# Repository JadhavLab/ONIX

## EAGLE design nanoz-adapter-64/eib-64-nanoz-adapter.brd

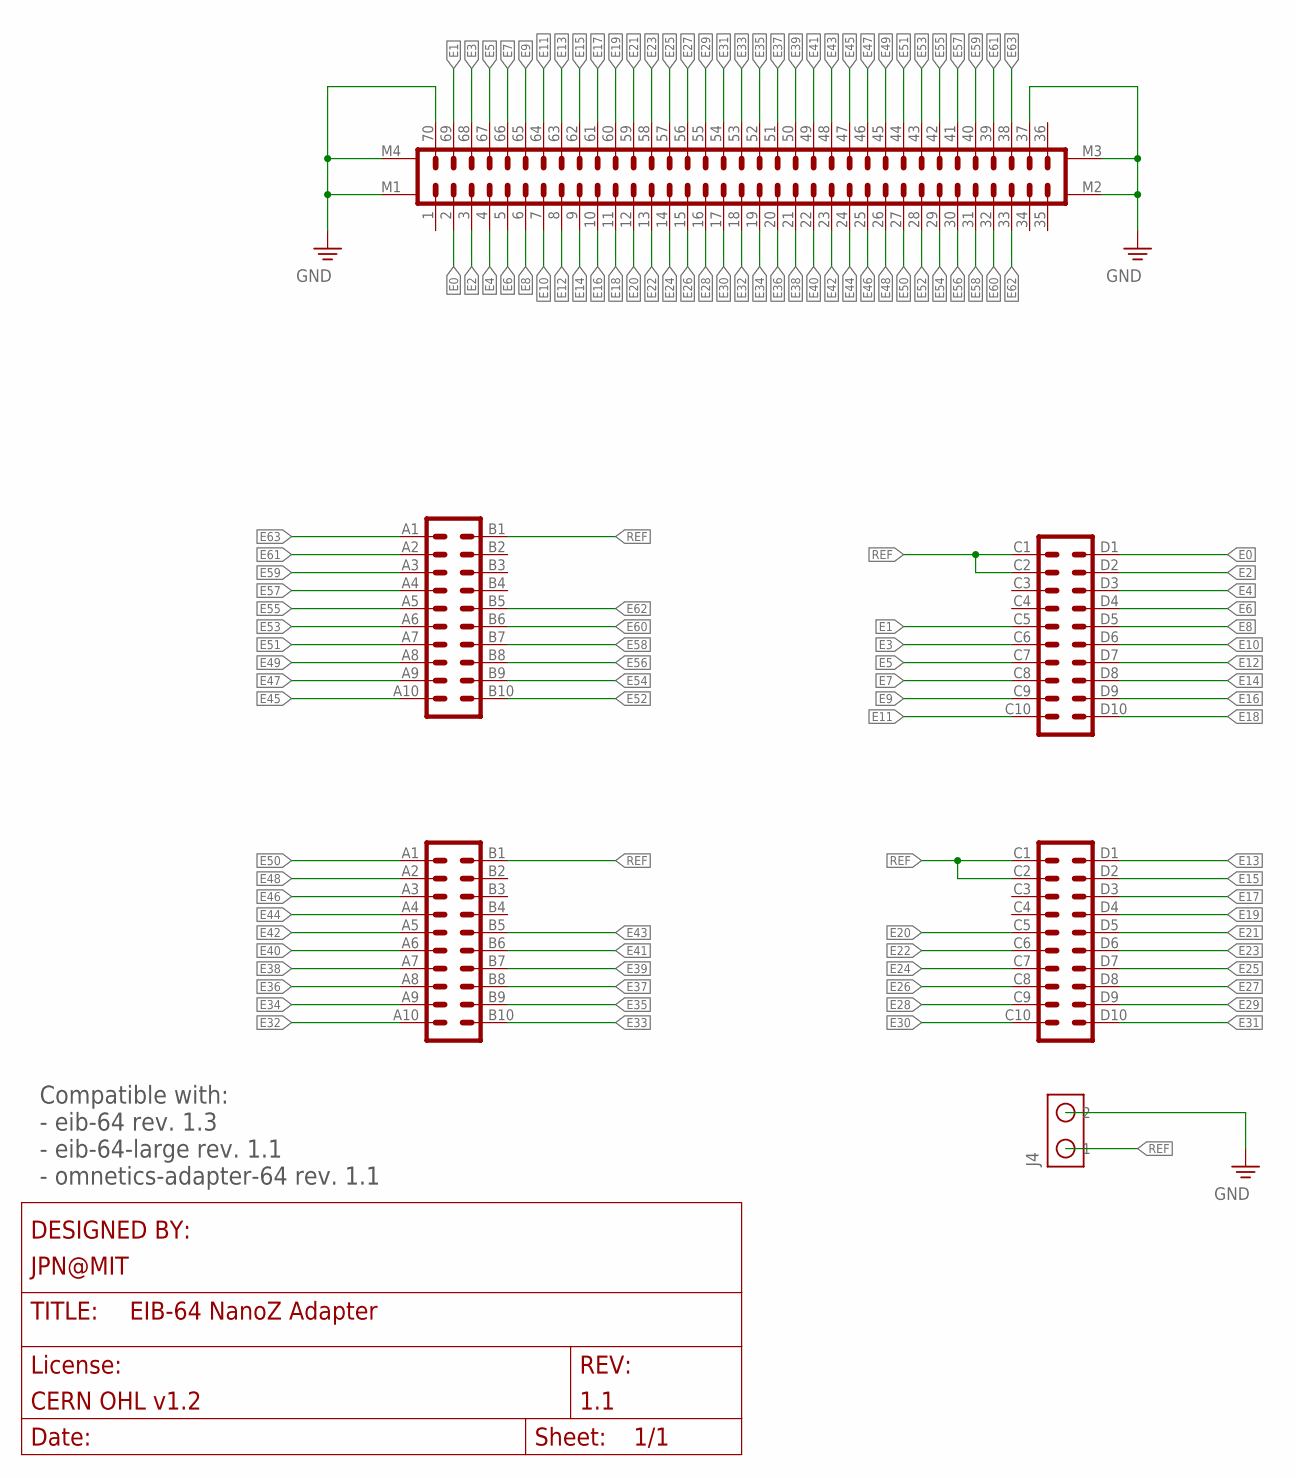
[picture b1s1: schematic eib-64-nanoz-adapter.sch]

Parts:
J1: DF40-REC; DF40-70HEAD
J2, J3: PINHD-4X10_MOLC-THRU; MOLC-110-11-S-Q
J4: SCREW2

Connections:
E0: J1.2, J2.D1 (20)
E1: J1.69, J2.C5 (5)
E2: J1.3, J2.D2 (19)
E3: J1.68, J2.C6 (6)
E4: J1.4, J2.D3 (18)
E5: J1.67, J2.C7 (7)
E6: J1.5, J2.D4 (17)
E7: J1.66, J2.C8 (8)
E8: J1.6, J2.D5 (16)
E9: J1.65, J2.C9 (9)
E10: J1.7, J2.D6 (15)
E11: J1.64, J2.C10 (10)
E12: J1.8, J2.D7 (14)
E13: J1.63, J3.D1 (20)
E14: J1.9, J2.D8 (13)
E15: J1.62, J3.D2 (19)
E16: J1.10, J2.D9 (12)
E17: J1.61, J3.D3 (18)
E18: J1.11, J2.D10 (11)
E19: J1.60, J3.D4 (17)
E20: J1.12, J3.C5 (5)
E21: J1.59, J3.D5 (16)
E22: J1.13, J3.C6 (6)
E23: J1.58, J3.D6 (15)
E24: J1.14, J3.C7 (7)
E25: J1.57, J3.D7 (14)
E26: J1.15, J3.C8 (8)
E27: J1.56, J3.D8 (13)
E28: J1.16, J3.C9 (9)
E29: J1.55, J3.D9 (12)
E30: J1.17, J3.C10 (10)
E31: J1.54, J3.D10 (11)
E32: J1.18, J3.A10 (10)
E33: J1.53, J3.B10 (11)
E34: J1.19, J3.A9 (9)
E35: J1.52, J3.B9 (12)
E36: J1.20, J3.A8 (8)
E37: J1.51, J3.B8 (13)
E38: J1.21, J3.A7 (7)
E39: J1.50, J3.B7 (14)
E40: J1.22, J3.A6 (6)
E41: J1.49, J3.B6 (15)
E42: J1.23, J3.A5 (5)
E43: J1.48, J3.B5 (16)
E44: J1.24, J3.A4 (4)
E45: J1.47, J2.A10 (10)
E46: J1.25, J3.A3 (3)
E47: J1.46, J2.A9 (9)
E48: J1.26, J3.A2 (2)
E49: J1.45, J2.A8 (8)
E50: J1.27, J3.A1 (1)
E51: J1.44, J2.A7 (7)
E52: J1.28, J2.B10 (11)
E53: J1.43, J2.A6 (6)
E54: J1.29, J2.B9 (12)
E55: J1.42, J2.A5 (5)
E56: J1.30, J2.B8 (13)
E57: J1.41, J2.A4 (4)
E58: J1.31, J2.B7 (14)
E59: J1.40, J2.A3 (3)
E60: J1.32, J2.B6 (15)
E61: J1.39, J2.A2 (2)
E62: J1.33, J2.B5 (16)
E63: J1.38, J2.A1 (1)
GND: J1.37, J1.70, J1.M1, J1.M2, J1.M3, J1.M4, J4.P$2 (2)
REF: J2.B1 (20), J2.C1 (1), J2.C2 (2), J3.B1 (20), J3.C1 (1), J3.C2 (2), J4.P$1 (1)

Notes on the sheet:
Compatible with: - eib-64 rev. 1.3 - eib-64-large rev. 1.1 - omnetics-adapter-64 rev. 1.1

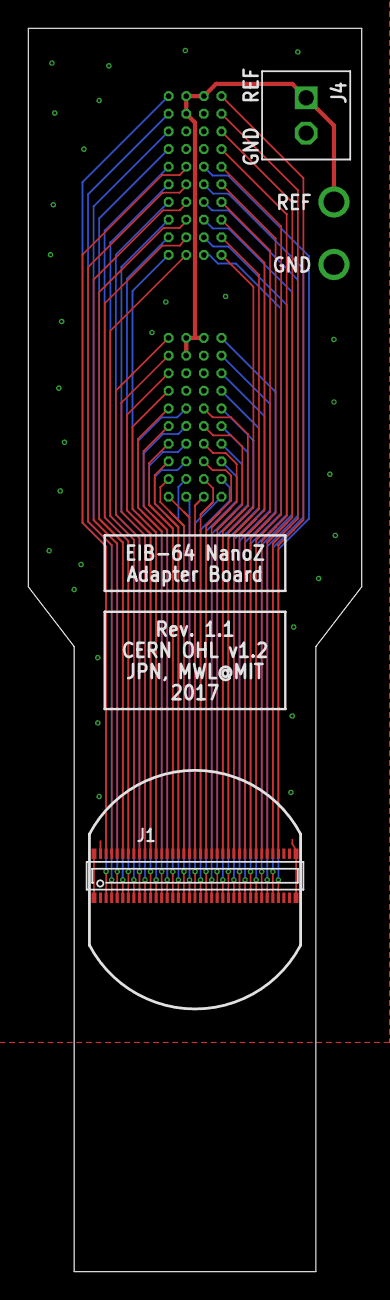
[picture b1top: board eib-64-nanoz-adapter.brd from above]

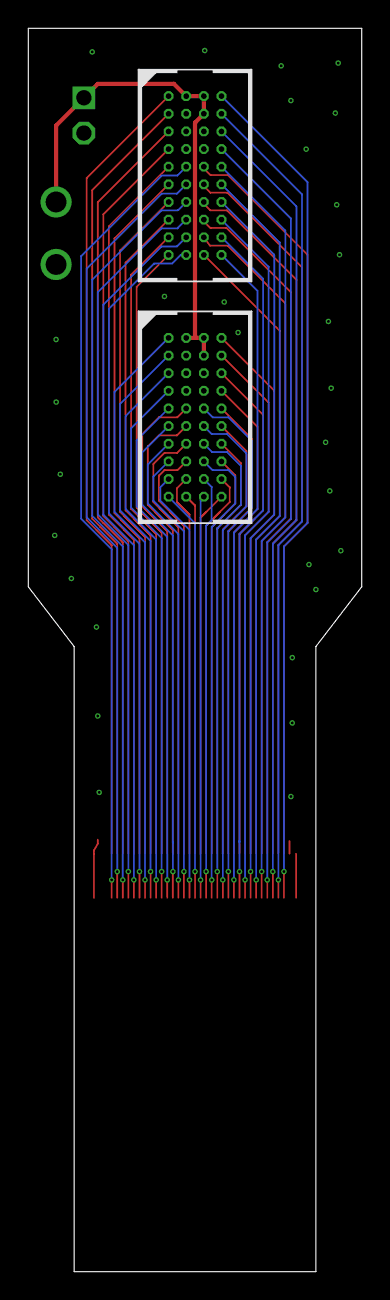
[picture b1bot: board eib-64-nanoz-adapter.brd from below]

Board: 4 copper layers, 24.0 x 89.5 mm, 4 parts (2 on the bottom side), 66 nets.

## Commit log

2021-06-07 elongated the footprint
2021-06-07 added ground plane, renamed file long for longer footprint
2021-06-08 updated long board to have top and bottom gnd planes

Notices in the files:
nanoz-adapter-64/eib-64-nanoz-adapter.brd:
CERN OHL v1.2
nanoz-adapter-64/eib-64-nanoz-adapter.sch:
LICENSE: CERN OHL v1.2
